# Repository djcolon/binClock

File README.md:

# binClock

**Daniel Colon - 19/02/2024**

A binary clock using an ESP8266 board with some 74HC595 shift registers to
drive LEDs.
Uses NTP to get time over the network.
Also has modes to show it's IP and ping-pong a led back and forth.

Built with an ESP32-C3 Mini, which I bought for 1.83
[here](https://www.aliexpress.com/item/1005005967641936.html)

[Built using PlatformIO](https://platformio.org/)

## Testing

To run tests you need to have configured the platformIO native environment.
See the [platformIO guides](https://piolabs.com/blog/insights/unit-testing-part-1.html)
for more detail.

After installation, run tests by navigating to `native > advanced > test` in the
platformIO sidebar.

## Board

The PCB and schematic do not include the LEDs. An 8-pin connector is offered,
as well as a mounting hole for the LED ground. The intention is to use a piece
of 2mm solid core copper to attach the LED ground to, with wires leading to an
8 pin connector which will plug into the PCB. The entire board can be powered
via the ESP32's USB-C connector.

## Images

The assembled binClock:

The prototype:

The schematic:

A preview of the PCB front:

The devboard pinout.

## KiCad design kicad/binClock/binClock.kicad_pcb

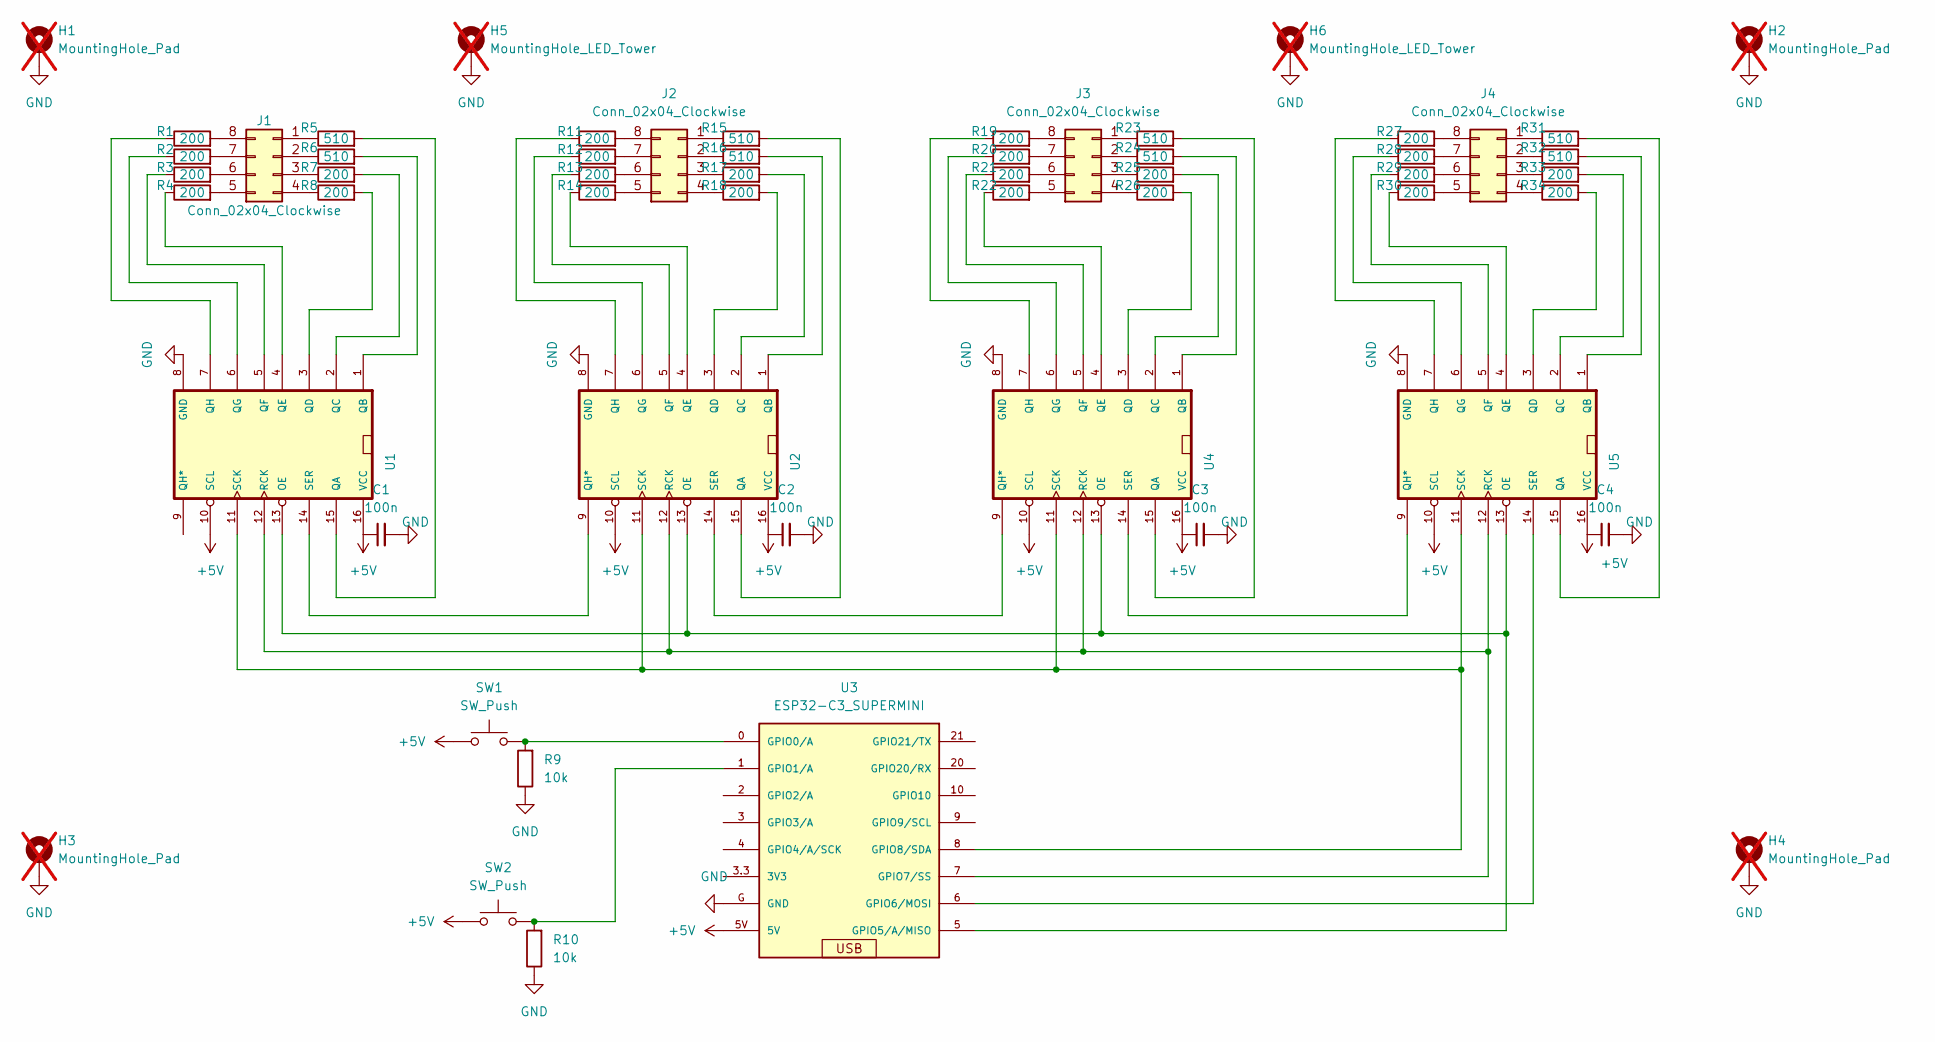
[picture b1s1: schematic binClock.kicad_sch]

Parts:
C1, C2, C3, C4: 100n; C_Disc_D3.0mm_W1.6mm_P2.50mm
H1, H2, H3, H4: MountingHole_Pad; MountingHole_2.7mm_M2.5_Pad_TopBottom; not fitted
H5, H6: MountingHole_LED_Tower; MountingHole_2.2mm_M2_Pad_TopBottom; not fitted
J1, J2, J3, J4: Conn_02x04_Clockwise; PinHeader_2x04_P2.54mm_Vertical_Clockwise
R1, R2, R3, R4, R7, R8, R11, R12, R13, R14, R17, R18, R19, R20, R21, R22, R25, R26, R27, R28, R29, R30, R33, R34: 200; R_Axial_DIN0207_L6.3mm_D2.5mm_P7.62mm_Horizontal
R5, R6, R15, R16, R23, R24, R31, R32: 510; R_Axial_DIN0207_L6.3mm_D2.5mm_P7.62mm_Horizontal
R9, R10: 10k; R_Axial_DIN0207_L6.3mm_D2.5mm_P7.62mm_Horizontal
SW1, SW2: SW_Push; SW_PUSH_6mm
U1, U2, U4, U5: 74HC595N; DIP16-2.54-20.32X5.84MM; MPN 74HC595N
U3: ESP32-C3_SUPERMINI; MODULE_ESP32-C3_SUPERMINI

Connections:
+5V: C1.1, C2.1, C3.1, C4.1, SW1.1, SW2.1, U1.10 (SCL), U1.16 (VCC), U2.10 (SCL), U2.16 (VCC), U3.5V, U4.10 (SCL), U4.16 (VCC), U5.10 (SCL), U5.16 (VCC)
GND: C1.2, C2.2, C3.2, C4.2, H1.1, H2.1, H3.1, H4.1, H5.1, H6.1, R9.1, R10.1, U1.8 (GND), U2.8 (GND), U3.G (GND), U4.8 (GND), U5.8 (GND)
unnamed: J1.1, R5.1
unnamed: J1.2, R6.1
unnamed: J1.3, R7.1
unnamed: J1.4, R8.1
unnamed: J1.5, R4.2
unnamed: J1.6, R3.2
unnamed: J1.7, R2.2
unnamed: J1.8, R1.2
unnamed: J2.1, R15.1
unnamed: J2.2, R16.1
unnamed: J2.3, R17.1
unnamed: J2.4, R18.1
unnamed: J2.5, R14.2
unnamed: J2.6, R13.2
unnamed: J2.7, R12.2
unnamed: J2.8, R11.2
unnamed: J3.1, R23.1
unnamed: J3.2, R24.1
unnamed: J3.3, R25.1
unnamed: J3.4, R26.1
unnamed: J3.5, R22.2
unnamed: J3.6, R21.2
unnamed: J3.7, R20.2
unnamed: J3.8, R19.2
unnamed: J4.1, R31.1
unnamed: J4.2, R32.1
unnamed: J4.3, R33.1
unnamed: J4.4, R34.1
unnamed: J4.5, R30.2
unnamed: J4.6, R29.2
unnamed: J4.7, R28.2
unnamed: J4.8, R27.2
unnamed: U1.13 (OE), U2.13 (OE), U3.5 (GPIO5/A/MISO), U4.13 (OE), U5.13 (OE)
unnamed: R5.2, U1.15 (QA)
unnamed: R6.2, U1.1 (QB)
unnamed: R7.2, U1.2 (QC)
unnamed: R8.2, U1.3 (QD)
unnamed: R4.1, U1.4 (QE)
unnamed: R3.1, U1.5 (QF)
unnamed: R2.1, U1.6 (QG)
unnamed: R1.1, U1.7 (QH)
unnamed: U1.12 (RCK), U2.12 (RCK), U3.7 (GPIO7/SS), U4.12 (RCK), U5.12 (RCK)
unnamed: U1.11 (SCK), U2.11 (SCK), U3.8 (GPIO8/SDA), U4.11 (SCK), U5.11 (SCK)
unnamed: U1.14 (SER), U2.9 (QH*)
unnamed: R15.2, U2.15 (QA)
unnamed: R16.2, U2.1 (QB)
unnamed: R17.2, U2.2 (QC)
unnamed: R18.2, U2.3 (QD)
unnamed: R14.1, U2.4 (QE)
unnamed: R13.1, U2.5 (QF)
unnamed: R12.1, U2.6 (QG)
unnamed: R11.1, U2.7 (QH)
unnamed: U2.14 (SER), U4.9 (QH*)
unnamed: R9.2, SW1.2, U3.0 (GPIO0/A)
unnamed: R10.2, SW2.2, U3.1 (GPIO1/A)
unnamed: U3.6 (GPIO6/MOSI), U5.14 (SER)
unnamed: R23.2, U4.15 (QA)
unnamed: R24.2, U4.1 (QB)
unnamed: R25.2, U4.2 (QC)
unnamed: R26.2, U4.3 (QD)
unnamed: R22.1, U4.4 (QE)
unnamed: R21.1, U4.5 (QF)
unnamed: R20.1, U4.6 (QG)
unnamed: R19.1, U4.7 (QH)
unnamed: U4.14 (SER), U5.9 (QH*)
unnamed: R31.2, U5.15 (QA)
unnamed: R32.2, U5.1 (QB)
unnamed: R33.2, U5.2 (QC)
unnamed: R34.2, U5.3 (QD)
unnamed: R30.1, U5.4 (QE)
unnamed: R29.1, U5.5 (QF)
unnamed: R28.1, U5.6 (QG)
unnamed: R27.1, U5.7 (QH)

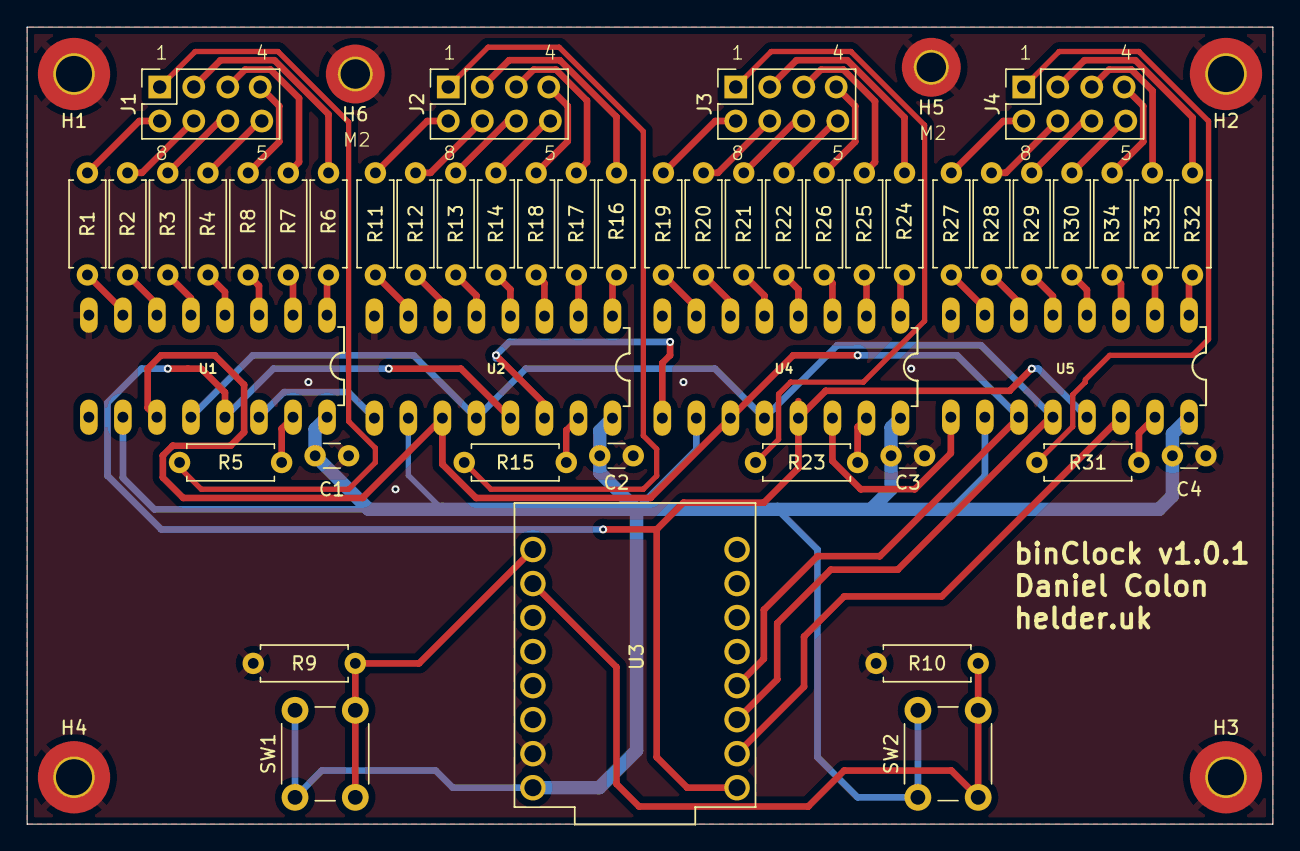
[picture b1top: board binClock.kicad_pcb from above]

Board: 2 copper layers, 93.0 x 59.5 mm, 55 parts (0 on the bottom side), 75 nets.

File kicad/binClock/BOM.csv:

"Reference","Value","Qty","DNP"
"C1,C2,C3,C4","100n","4",""
"J1,J2,J3,J4","Conn_02x04_Clockwise","4",""
"R1,R2,R3,R4,R7,R8,R11,R12,R13,R14,R17,R18,R19,R20,R21,R22,R25,R26,R27,R28,R29,R30,R33,R34","200","24",""
"R5,R6,R15,R16,R23,R24,R31,R32","510","8",""
"R9,R10","10k","2",""
"SW1,SW2","SW_Push","2",""
"U1,U2,U4,U5","74HC595N","4",""
"U3","ESP32-C3_SUPERMINI","1",""

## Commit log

2024-02-19 Added readme
2024-02-19 Connecting to WiFI with captive portal using WiFiManager
2024-02-20 Rewrote to have actual clock functionality.
2024-02-20 Using built-in NTP to set time.
2024-02-21 Experimenting with shiftout function. Added some output ni setup to give visual without serial.
2024-02-22 Enabled all 4 registers with new extendd prototype.
2024-02-23 Some work on shfirout function, will need to get the scope out to find reason for unpredictable behaviour on some of the regsiters.
2024-02-23 Added pingpong mode. Debugged custom shiftout
2024-02-25 Added mode to show ip, set up mDNS
2024-02-25 Added buttons to switch modes and reset wifi settings
2024-02-25 Added image of prototype to README.
2024-02-25 Resetting registers on any mode switch.
2024-02-26 Ported to ESP32-C3 Mini
2024-02-26 Added link to chip in README
2024-02-29 Started work on schematic and PCB
2024-03-01 Work on schematic, added chip image
2024-03-02 Finished schematic and board layout. Included gerbers. Ordered board from jlcpcb.
2024-03-02 Saved changes of fill areas after gerber generation
2024-03-02 Changed pins to match new schematic. Added OE pin, and brightness settings.
2024-03-02 Added always on mode to troubleshoot LEDs. Shortened loop delays to increase button responsiveness.
2024-03-02 Set binClock to default mode. Updated prototype photo.
2024-03-05 Cleaned up, and pulled resgiters into won file.
2024-03-05 Defined interface for various modes that we will use to manage them.
2024-03-05 Further fleshed out ModeInterface.
2024-03-05 Added mode class for allOn.
2024-03-06 Work on abstarction layer for modes.
2024-03-06 Ported pingpong to managed mode.
2024-03-06 Added template for modes.
2024-03-06 Added showIp mode
2024-03-07 Refactored application to use ModeManager.
2024-03-07 Started work on unit tests for ModeManager.
2024-03-07 Fixed last bugs to get modeManager functional.
2024-03-07 Using non-blocking mechanism for delay. Further test code for ModeManager.
2024-03-14 Added values to components. Added photo of assembled PCB and BOM
2024-03-17 Added files for template used to create LED tree.
2024-03-17 Added center marks to holes on template
2024-03-17 Fixed orientation of tree template PDF.
2024-03-17 Added centerline to wire in tree template PDF.
2024-03-17 Corrected error in schematic and recreated production files
2024-03-17 Added photo of working device.
2024-03-17 Updated images
2024-03-17 Saved last changes to board and board settings.
